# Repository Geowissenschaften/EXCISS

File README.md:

# EXCISS
Experimental Chondrule Formation at the International Space Station 

Documentation is still beeing updated.

The circuit design files are online, the mechanical design files will be next.

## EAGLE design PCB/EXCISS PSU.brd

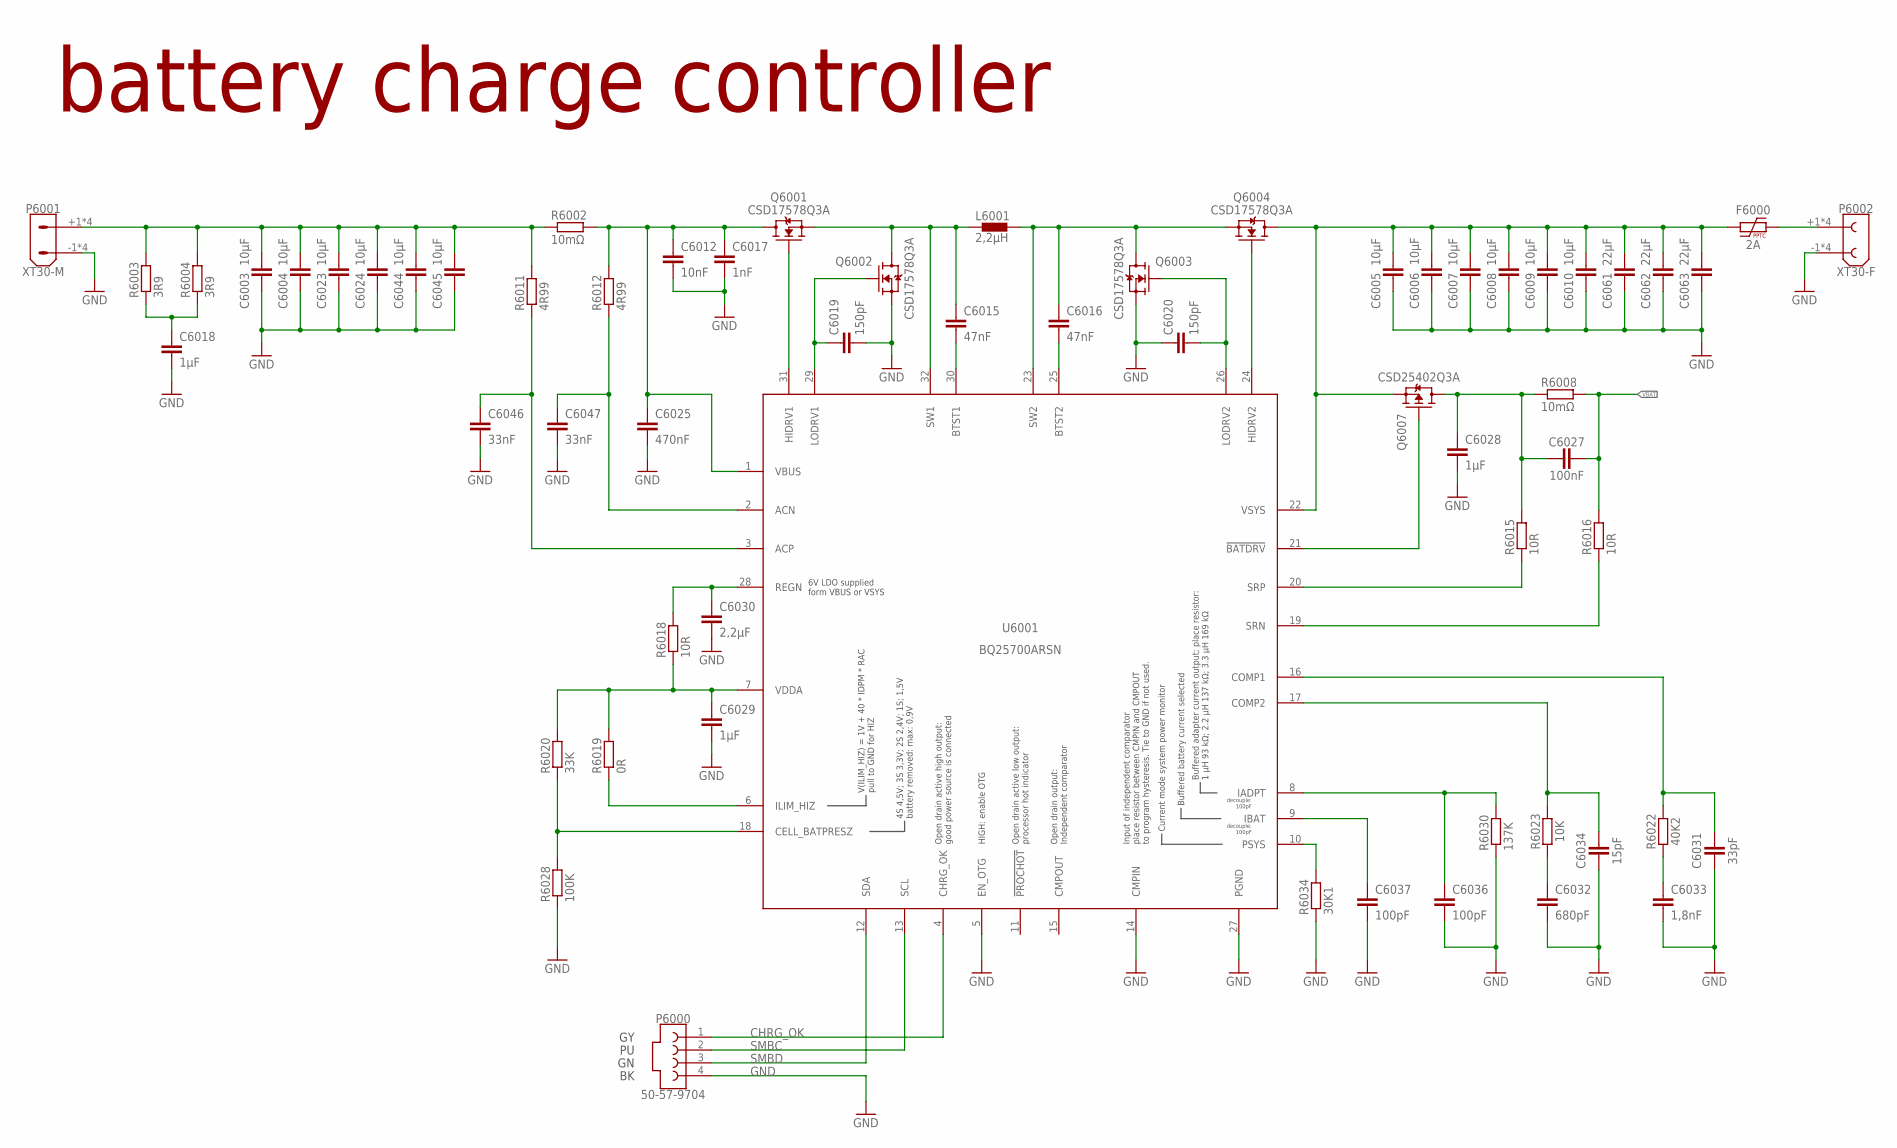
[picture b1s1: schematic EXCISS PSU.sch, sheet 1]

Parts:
C6003, C6004, C6005, C6006, C6007, C6008, C6009, C6010, C6023, C6024, C6044, C6045: 10µF; C0805
C6012: 10nF; C0603
C6015, C6016: 47nF; C0603
C6017: 1nF; C0603
C6018, C6028, C6029: 1µF; C0603
C6019, C6020: 150pF; C0603
C6025: 470nF; C0805
C6027: 100nF; C0603
C6030: 2,2µF; C0603
C6031: 33pF; C0603
C6032: 680pF; C0603
C6033: 1,8nF; C0603
C6034: 15pF; C0603
C6036, C6037: 100pF; C0603
C6046, C6047: 33nF; C0603
C6061, C6062, C6063: 22µF; C1210
F6000: 2A; PTC_1812
L6001: 2,2µH; 8030
P6000: 50-57-9704; RENAME-SIGNAL
P6001: XT30-M; RENAME_XT-CONNECTOR
P6002: XT30-F; RENAME_XT-CONNECTOR
Q6001, Q6002, Q6003, Q6004: CSD17578Q3A; Q3A
Q6007: CSD25402Q3A; Q3A
R6002, R6008: 10mΩ; R1206
R6003, R6004: 3R9; R1206
R6011, R6012: 4R99; R0603
R6015, R6016, R6018: 10R; R0603
R6019: 0R; R0603
R6020: 33K; R0603
R6022: 40K2; R0603
R6023: 10K; R0603
R6028: 100K; R0603
R6030: 137K; R0603
R6034: 30K1; R0603
U6001: BQ25700ARSN; RSN(S-PWQFN-N32)

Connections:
CHRG_OK: P6000.1, U6001.4 (CHRG_OK)
GND: C6003.2, C6004.2, C6005.2, C6006.2, C6007.2, C6008.2, C6009.2, C6010.2, C6012.2, C6017.2, C6018.2, C6019.2, C6020.1, C6023.2, C6024.2, C6025.2, C6028.2, C6029.2, C6030.2, C6031.2, C6032.2, C6033.2, C6034.2, C6036.2, C6037.2, C6044.2, C6045.2, C6046.2, C6047.2, C6061.2, C6062.2, C6063.2, P6000.4, P6001.-1 (-), P6001.-2 (-), P6001.-3 (-), P6001.-4 (-), P6002.-1 (-), P6002.-2 (-), P6002.-3 (-), P6002.-4 (-), Q6002.1 (S), Q6002.2 (S), Q6002.3 (S), Q6003.1 (S), Q6003.2 (S), Q6003.3 (S), R6028.1, R6030.1, R6034.1, U6001.5 (EN_OTG), U6001.14 (CMPIN), U6001.27 (PGND), U6001.TP0 (GND), U6001.TP1 (GND), U6001.TP2 (GND), U6001.TP3 (GND), U6001.TP4 (GND), U6001.TP5 (GND), U6001.TP6 (GND), U6001.TP7 (GND), U6001.TP8 (GND), U6001.TP9 (GND); also elsewhere on the board
ISS_VBUS: C6003.1, C6004.1, C6023.1, C6024.1, C6044.1, C6045.1, P6001.+1 (+), P6001.+2 (+), P6001.+3 (+), P6001.+4 (+), R6002.1, R6003.2, R6004.2, R6011.2; also elsewhere on the board
unnamed: C6018.1, R6003.1, R6004.1
unnamed: Q6007.4 (G), U6001.21 (!BATDRV)
unnamed: C6032.1, R6023.1
unnamed: R6015.1, U6001.20 (SRP)
unnamed: C6027.1, C6028.1, Q6007.1 (D), Q6007.2 (D), Q6007.3 (D), R6008.1, R6015.2
unnamed: R6016.1, U6001.19 (SRN)
unnamed: Q6001.4 (G), U6001.31 (HIDRV1)
unnamed: C6019.1, Q6002.4 (G), U6001.29 (LODRV1)
unnamed: C6015.2, U6001.30 (BTST1)
unnamed: C6016.1, L6001.P$2 (2), Q6003.TP0 (D), Q6003.TP1 (D), Q6003.TP2 (D), Q6003.TP3 (D), Q6003.TP4 (D), Q6003.TP5 (D), Q6003.TP6 (D), Q6003.TP7 (D), Q6004.1 (S), Q6004.2 (S), Q6004.3 (S), U6001.23 (SW2)
unnamed: C6034.1, R6023.2, U6001.17 (COMP2)
unnamed: C6036.1, R6030.2, U6001.8 (IADPT)
unnamed: R6019.1, U6001.6 (ILIM_HIZ)
unnamed: C6033.1, R6022.1
unnamed: C6020.2, Q6003.4 (G), U6001.26 (LODRV2)
unnamed: Q6004.4 (G), U6001.24 (HIDRV2)
unnamed: C6031.1, R6022.2, U6001.16 (COMP1)
unnamed: C6015.1, L6001.P$1 (1), Q6001.1 (S), Q6001.2 (S), Q6001.3 (S), Q6002.TP0 (D), Q6002.TP1 (D), Q6002.TP2 (D), Q6002.TP3 (D), Q6002.TP4 (D), Q6002.TP5 (D), Q6002.TP6 (D), Q6002.TP7 (D), U6001.32 (SW1)
unnamed: R6034.2, U6001.10 (PSYS)
unnamed: C6037.1, U6001.9 (IBAT)
unnamed: C6046.1, R6011.1, U6001.3 (ACP)
unnamed: C6047.1, R6012.1, U6001.2 (ACN)
unnamed: C6016.2, U6001.25 (BTST2)
unnamed: C6012.1, C6017.1, C6025.1, Q6001.TP0 (D), Q6001.TP1 (D), Q6001.TP2 (D), Q6001.TP3 (D), Q6001.TP4 (D), Q6001.TP5 (D), Q6001.TP6 (D), Q6001.TP7 (D), R6002.2, R6012.2, U6001.1 (VBUS)
unnamed: R6020.1, R6028.2, U6001.18 (CELL_BATPRESZ)
REGN: C6030.1, R6018.2, U6001.28 (REGN)
SMBC: P6000.2, U6001.13 (SCL); also elsewhere on the board
SMBD: P6000.3, U6001.12 (SDA); also elsewhere on the board
VBAT: C6027.2, R6008.2, R6016.2; also elsewhere on the board
VDDA: C6029.1, R6018.1, R6019.2, R6020.2, U6001.7 (VDDA)
VSYS_UPS: F6000.P$3 (2), P6002.+1 (+), P6002.+2 (+), P6002.+3 (+), P6002.+4 (+); also elsewhere on the board
VSYS_UPS_PREFUSE: C6005.1, C6006.1, C6007.1, C6008.1, C6009.1, C6010.1, C6061.1, C6062.1, C6063.1, F6000.P$2 (1), Q6004.TP0 (D), Q6004.TP1 (D), Q6004.TP2 (D), Q6004.TP3 (D), Q6004.TP4 (D), Q6004.TP5 (D), Q6004.TP6 (D), Q6004.TP7 (D), Q6007.TP0 (S), Q6007.TP1 (S), Q6007.TP2 (S), Q6007.TP3 (S), Q6007.TP4 (S), Q6007.TP5 (S), Q6007.TP6 (S), Q6007.TP7 (S), U6001.22 (VSYS)

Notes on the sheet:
battery charge controller

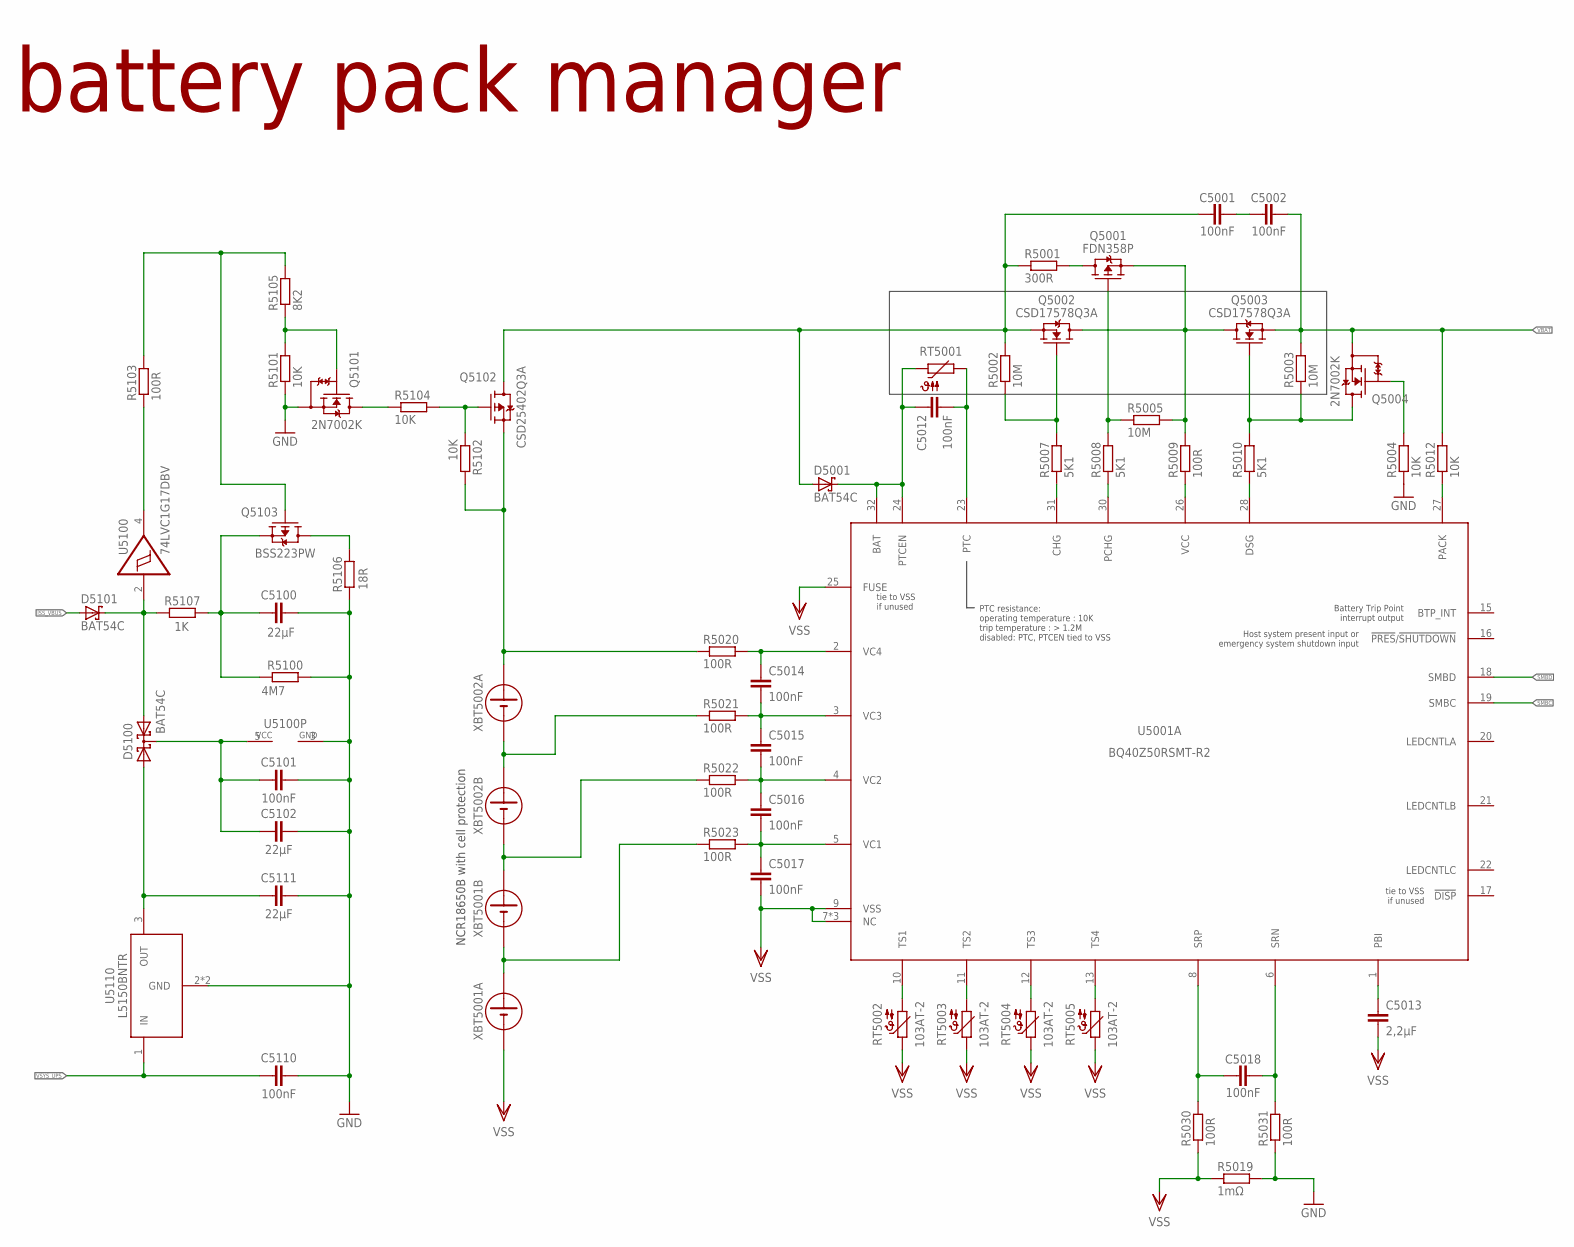
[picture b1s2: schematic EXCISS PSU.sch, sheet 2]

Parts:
C5001, C5002, C5012, C5014, C5015, C5016, C5017, C5018, C5101, C5110: 100nF; C0603
C5013: 2,2µF; C0805
C5100, C5102, C5111: 22µF; C0805
D5001, D5100, D5101: BAT54C; SOT23
Q5001: FDN358P; SOT23-3
Q5002, Q5003: CSD17578Q3A; Q3A
Q5004, Q5101: 2N7002K; SOT23-3
Q5102: CSD25402Q3A; Q3A
Q5103: BSS223PW; DCK(R-PDSO-G3)
R5001: 300R; R2512
R5002, R5003, R5005: 10M; R0603
R5004, R5012, R5101, R5102, R5104: 10K; R0603
R5007, R5008, R5010: 5K1; R0603
R5009, R5020, R5021, R5022, R5023, R5030, R5031, R5103: 100R; R0603
R5019: 1mΩ; R1206
R5100: 4M7; R0805
R5105: 8K2; R0603
R5106: 18R; R0805
R5107: 1K; R0603
RT5001: PRF15BB103RB6RC; 0402
RT5002, RT5003, RT5004, RT5005: 103AT-2; AT-2
U5001: BQ40Z50RSMT-R2; RSM(S-PVQFN-N32)
U5100: 74LVC1G17DBV; SOT23-5
U5110: L5150BNTR; SOT223
XBT5001, XBT5002: KEYSTONE_1049_LONG

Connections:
1P: R5023.1, XBT5001.1+ (+), XBT5001.2- (-)
2P: R5022.1, XBT5001.2+ (+), XBT5002.2- (-)
3P: R5021.1, XBT5002.1- (-), XBT5002.2+ (+)
4P: Q5102.TP0 (S), Q5102.TP1 (S), Q5102.TP2 (S), Q5102.TP3 (S), Q5102.TP4 (S), Q5102.TP5 (S), Q5102.TP6 (S), Q5102.TP7 (S), R5020.1, R5102.2, XBT5002.1+ (+)
4P_SWITCHED: C5001.1, D5001.1 (A), Q5002.1 (S), Q5002.2 (S), Q5002.3 (S), Q5102.1 (D), Q5102.2 (D), Q5102.3 (D), R5001.1, R5002.2
GND: C5100.2, C5101.2, C5102.2, C5110.2, C5111.2, Q5101.2 (S), R5004.1, R5019.2, R5031.1, R5100.1, R5101.1, R5106.2, U5100.3 (GND), U5110.2 (GND), U5110.4 (GND); also elsewhere on the board
ISS_VBUS: D5101.1 (A); also elsewhere on the board
unnamed: Q5102.4 (G), R5102.1, R5104.2
unnamed: R5103.1, U5100.4 (O)
unnamed: Q5101.1 (G), R5101.2, R5105.1
unnamed: Q5101.3 (D), R5104.1
unnamed: C5100.1, Q5103.2 (S), R5100.2, R5107.1
unnamed: R5010.1, U5001.28 (DSG)
unnamed: C5001.2, C5002.1
unnamed: Q5001.2 (S), Q5002.TP0 (D), Q5002.TP1 (D), Q5002.TP2 (D), Q5002.TP3 (D), Q5002.TP4 (D), Q5002.TP5 (D), Q5002.TP6 (D), Q5002.TP7 (D), Q5003.TP0 (D), Q5003.TP1 (D), Q5003.TP2 (D), Q5003.TP3 (D), Q5003.TP4 (D), Q5003.TP5 (D), Q5003.TP6 (D), Q5003.TP7 (D), R5005.2, R5009.2
unnamed: Q5103.3 (D), R5106.1
unnamed: Q5002.4 (G), R5002.1, R5007.2
unnamed: R5007.1, U5001.31 (CHG)
unnamed: Q5001.3 (D), R5001.2
unnamed: Q5001.1 (G), R5005.1, R5008.2
unnamed: R5009.1, U5001.26 (VCC)
unnamed: C5101.1, C5102.1, D5100.3 (CC), U5100.5 (VCC)
unnamed: Q5003.4 (G), Q5004.3 (D), R5003.1, R5010.2
unnamed: R5008.1, U5001.30 (PCHG)
unnamed: Q5004.1 (G), R5004.2
unnamed: R5012.1, U5001.27 (PACK)
unnamed: C5014.1, R5020.2, U5001.2 (VC4)
unnamed: C5014.2, C5015.1, R5021.2, U5001.3 (VC3)
unnamed: C5015.2, C5016.1, R5022.2, U5001.4 (VC2)
unnamed: C5016.2, C5017.1, R5023.2, U5001.5 (VC1)
unnamed: C5013.1, U5001.1 (PBI)
unnamed: C5012.1, D5001.3 (C), RT5001.1, U5001.24 (PTCEN), U5001.32 (BAT)
unnamed: C5012.2, RT5001.2, U5001.23 (PTC)
unnamed: C5018.2, R5031.2, U5001.6 (SRN)
unnamed: C5018.1, R5030.2, U5001.8 (SRP)
unnamed: RT5002.P$2 (2), U5001.10 (TS1)
unnamed: RT5003.P$2 (2), U5001.11 (TS2)
unnamed: RT5004.P$2 (2), U5001.12 (TS3)
unnamed: RT5005.P$2 (2), U5001.13 (TS4)
unnamed: Q5103.1 (G), R5103.2, R5105.2
unnamed: D5100.1 (A1), D5101.3 (C), R5107.2, U5100.2 (I)
OUT: C5111.1, D5100.2 (A2), U5110.3 (OUT)
SMBC: U5001.19 (SMBC); also elsewhere on the board
SMBD: U5001.18 (SMBD); also elsewhere on the board
VBAT: C5002.2, Q5003.1 (S), Q5003.2 (S), Q5003.3 (S), Q5004.2 (S), R5003.2, R5012.2; also elsewhere on the board
VSS: C5013.2, C5017.2, R5019.1, R5030.1, RT5002.P$1 (1), RT5003.P$1 (1), RT5004.P$1 (1), RT5005.P$1 (1), U5001.7 (NC), U5001.9 (VSS), U5001.14 (NC), U5001.25 (FUSE), U5001.29 (NC), U5001.TP0 (VSS), U5001.TP1 (VSS), XBT5001.1- (-)
VSYS_UPS: C5110.1, U5110.1 (IN); also elsewhere on the board

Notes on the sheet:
battery pack manager
NCR18650B with cell protection

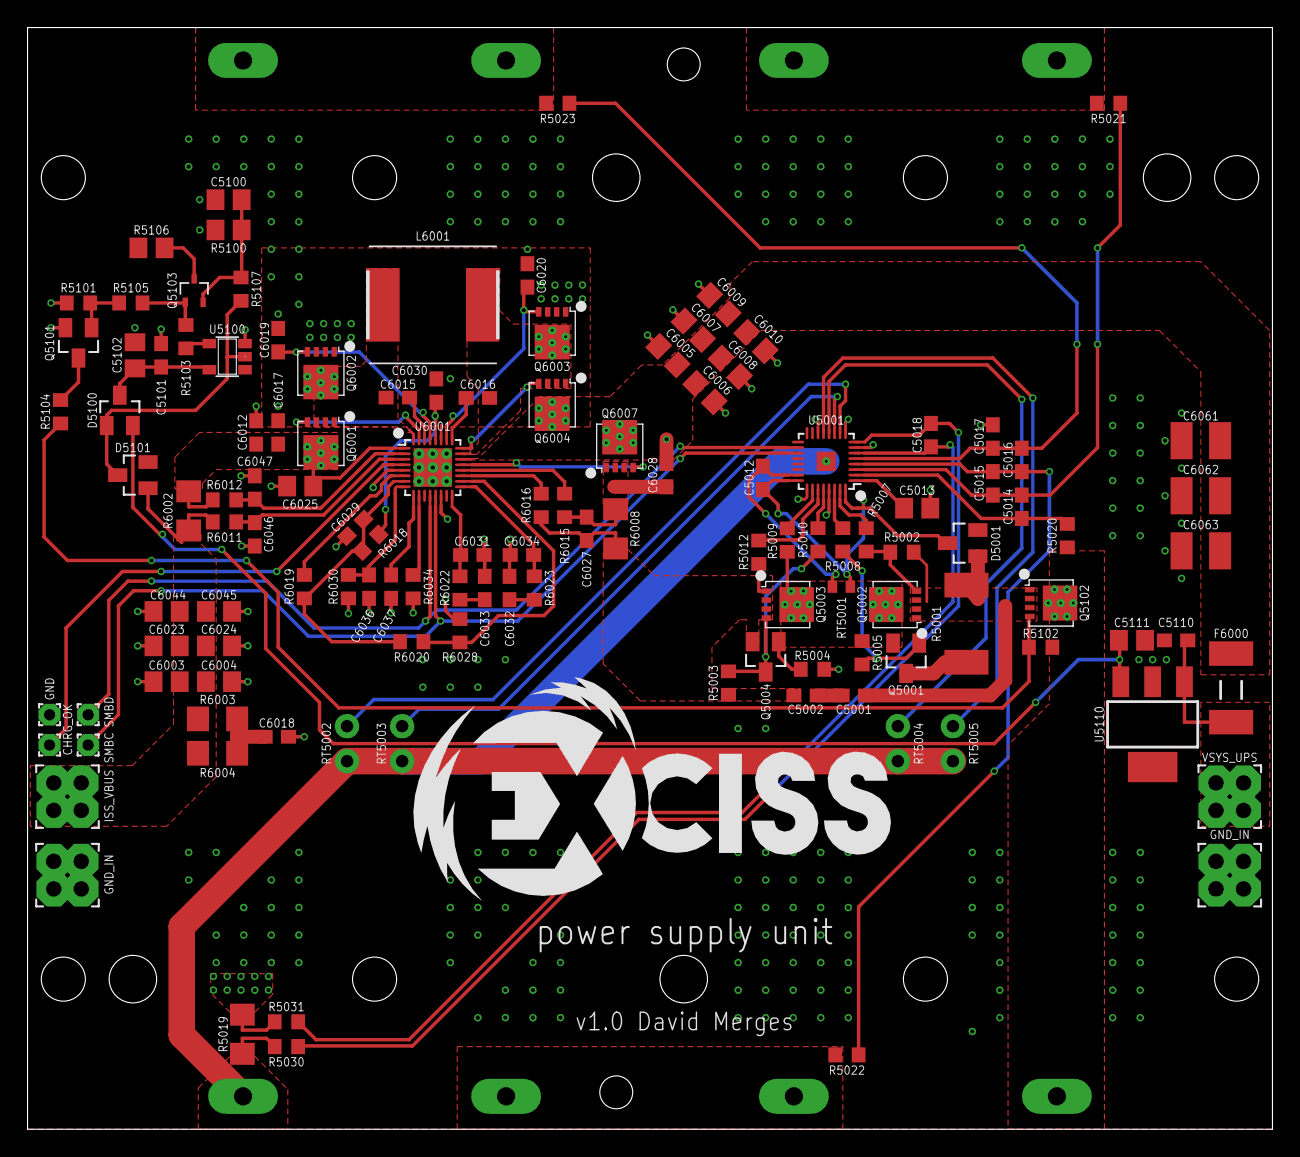
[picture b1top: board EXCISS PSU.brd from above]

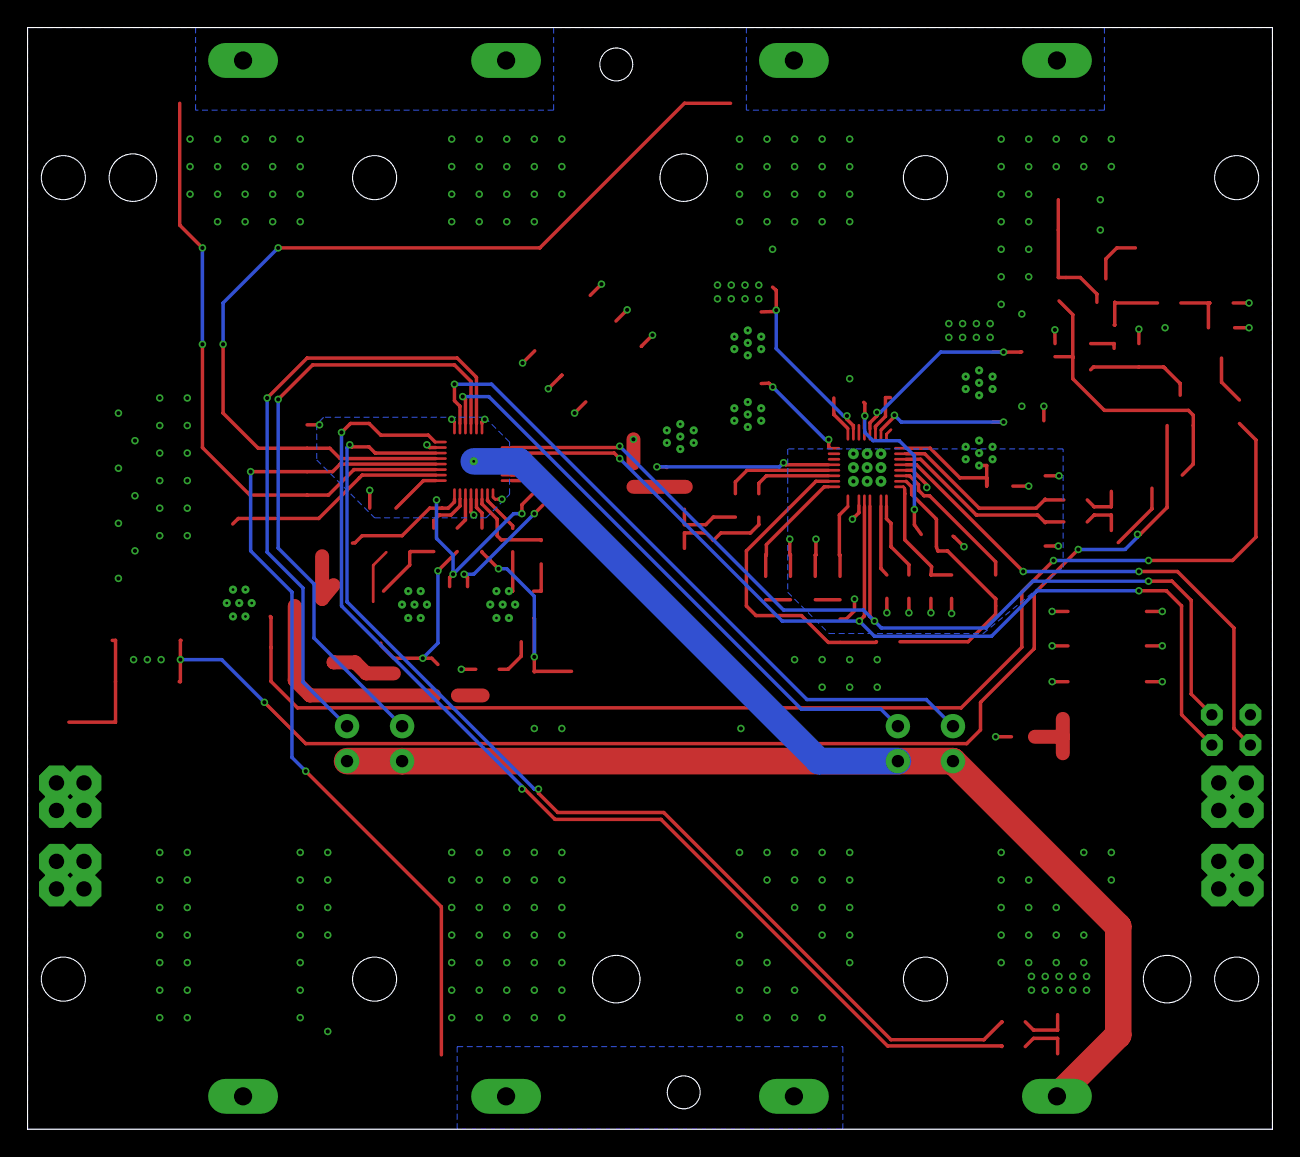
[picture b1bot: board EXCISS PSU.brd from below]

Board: 2 copper layers, 90.4 x 80.0 mm, 126 parts (2 on the bottom side), 76 nets.

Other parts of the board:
U$1, U$2, U$3, U$4: DRILL_M3_SPACER
U$5: LOGO_EXCISS

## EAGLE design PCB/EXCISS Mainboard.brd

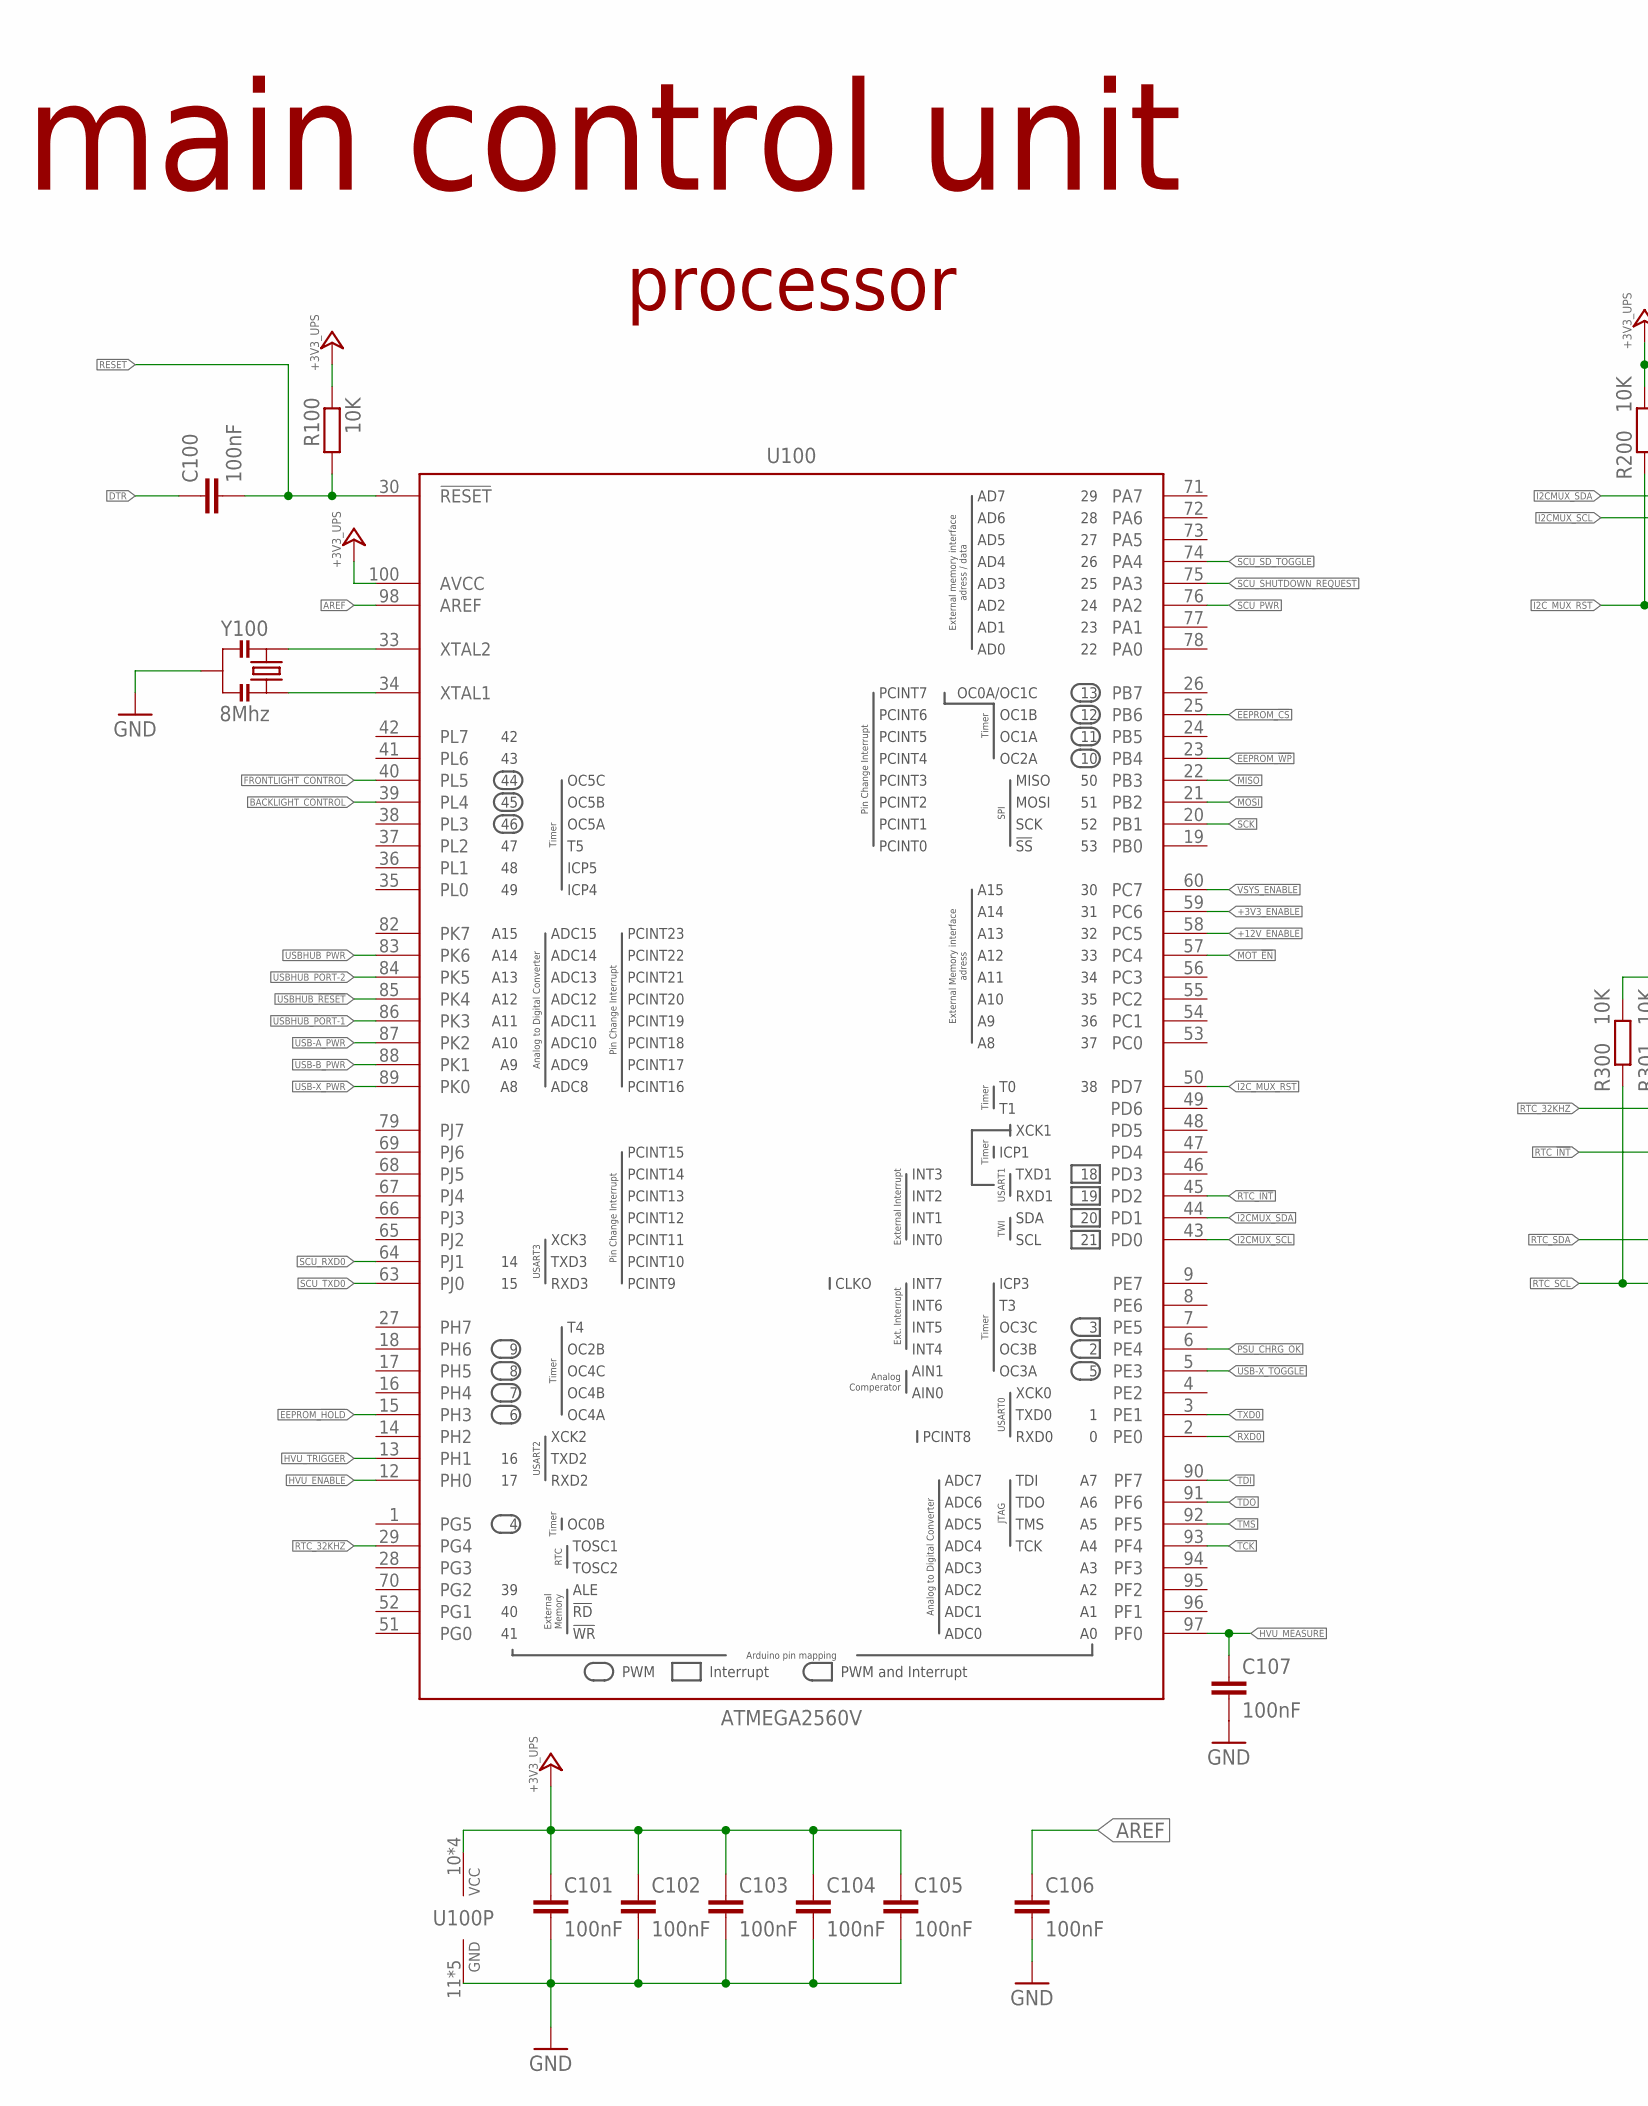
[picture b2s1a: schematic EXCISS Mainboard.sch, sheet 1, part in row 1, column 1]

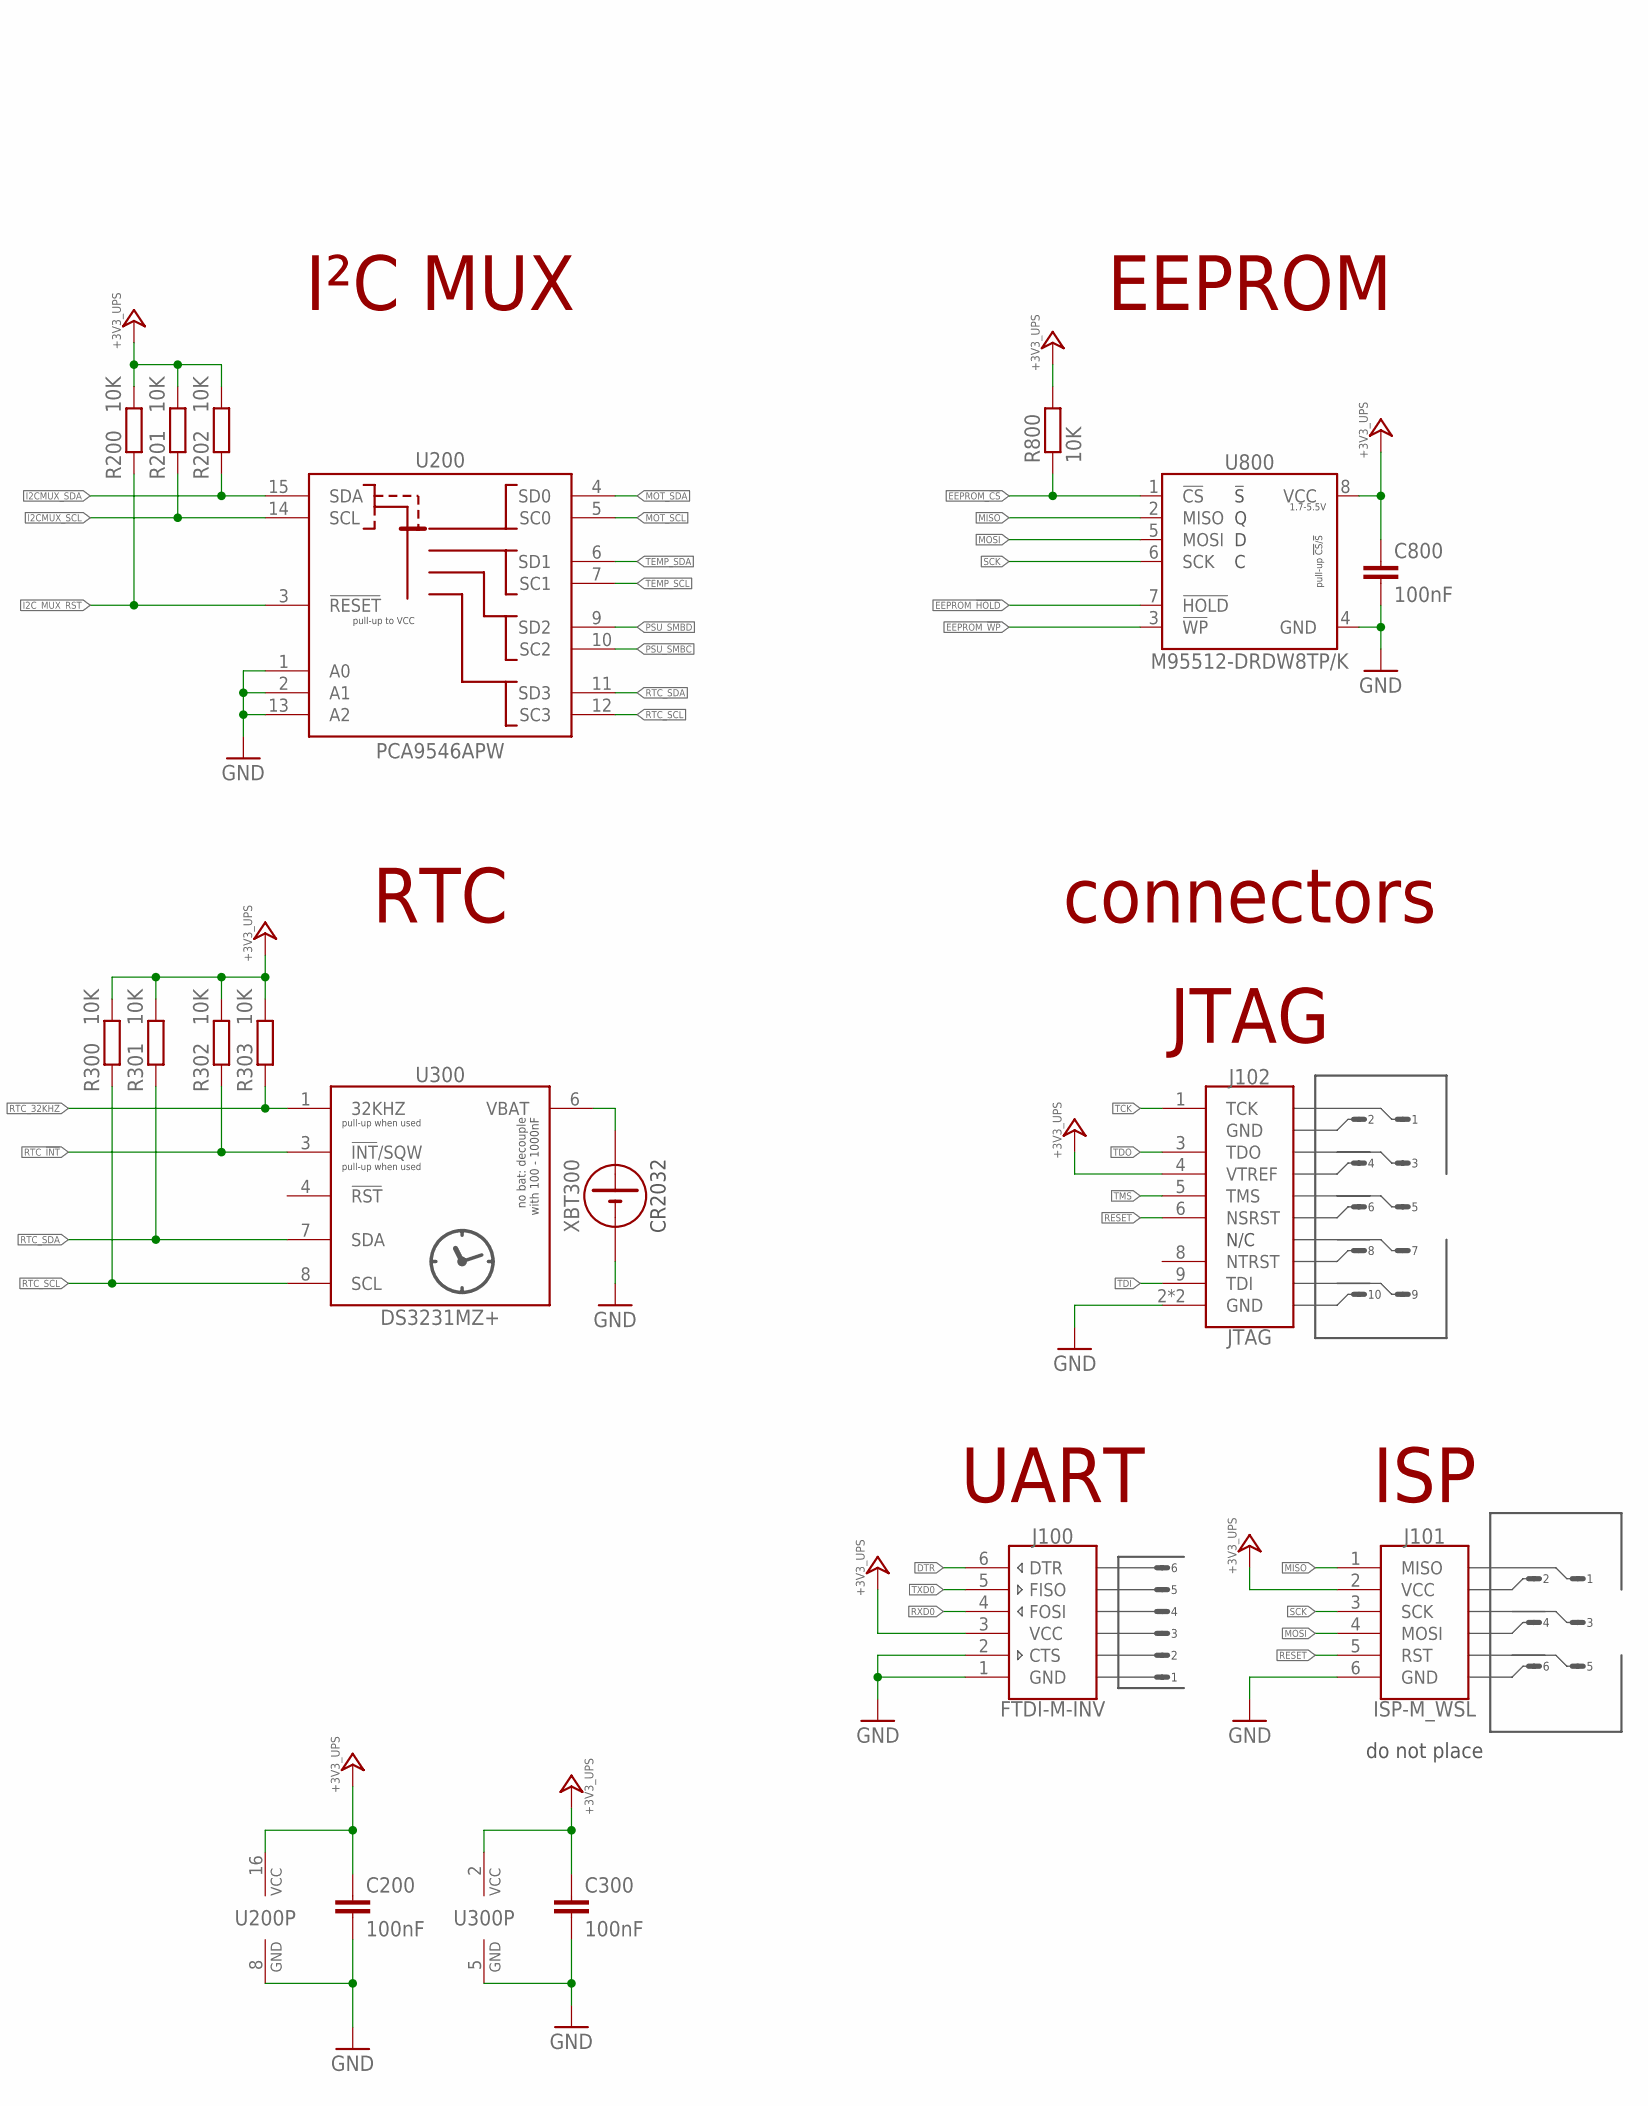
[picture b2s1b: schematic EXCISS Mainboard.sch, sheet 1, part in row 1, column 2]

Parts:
C100, C101, C102, C103, C104, C105, C106, C107, C200, C300, C800: 100nF; C0603
J100: FTDI-M-INV; MPE_094-1-006
J101: ISP-M_WSL; ISP-M-THT
J102: JTAG; 20021521-00010T1LF
R100, R200, R201, R202, R300, R301, R302, R303, R800: 10K; R0603
U100: ATMEGA2560V; TQFP100
U200: PCA9546APW; R-PDSO-G16
U300: DS3231MZ+; SOIC8
U800: M95512-DRDW8TP/K; TSSOP8
XBT300: KEYSTONE_1070
Y100: 8Mhz; CSTNE

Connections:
+3V3_ENABLE: U100.59 (PC6); also elsewhere on the board
+3V3_UPS: C101.1, C102.1, C103.1, C104.1, C105.1, C200.1, C300.1, C800.1, J100.3 (VCC), J101.2 (VCC), J102.4 (VTREF), R100.1, R200.1, R201.1, R202.1, R300.1, R301.1, R302.1, R303.1, R800.2, U100.10 (VCC), U100.31 (VCC), U100.61 (VCC), U100.80 (VCC), U100.100 (AVCC), U200.16 (VCC), U300.2 (VCC), U800.8 (VCC); also elsewhere on the board
+12V_ENABLE: U100.58 (PC5); also elsewhere on the board
AREF: C106.1, U100.98 (AREF)
BACKLIGHT_CONTROL: U100.39 (PL4); also elsewhere on the board
DTR: C100.1, J100.6 (DTR)
EEPROM_!CS: R800.1, U100.25 (PB6), U800.1 (!CS)
EEPROM_!HOLD: U100.15 (PH3), U800.7 (!HOLD)
EEPROM_!WP: U100.23 (PB4), U800.3 (!WP)
FRONTLIGHT_CONTROL: U100.40 (PL5); also elsewhere on the board
GND: C101.2, C102.2, C103.2, C104.2, C105.2, C106.2, C107.2, C200.2, C300.2, C800.2, J100.1 (GND), J100.2 (CTS), J101.6 (GND), J102.2 (GND), J102.10 (GND), U100.11 (GND), U100.32 (GND), U100.62 (GND), U100.81 (GND), U100.99 (GND), U200.1 (A0), U200.2 (A1), U200.8 (GND), U200.13 (A2), U300.5 (GND), U800.4 (GND), XBT300.-, Y100.2; also elsewhere on the board
HVU_ENABLE: U100.12 (PH0); also elsewhere on the board
HVU_MEASURE: C107.1, U100.97 (PF0); also elsewhere on the board
HVU_TRIGGER: U100.13 (PH1); also elsewhere on the board
I2CMUX_SCL: R201.2, U100.43 (PD0), U200.14 (SCL)
I2CMUX_SDA: R202.2, U100.44 (PD1), U200.15 (SDA)
I2C_MUX_RST: R200.2, U100.50 (PD7), U200.3 (!RESET)
MISO: J101.1 (MISO), U100.22 (PB3), U800.2 (MISO)
MOSI: J101.4 (MOSI), U100.21 (PB2), U800.5 (MOSI)
MOT_!EN: U100.57 (PC4); also elsewhere on the board
MOT_SCL: U200.5 (SC0); also elsewhere on the board
MOT_SDA: U200.4 (SD0); also elsewhere on the board
unnamed: U300.6 (VBAT), XBT300.+
unnamed: U100.33 (XTAL2), Y100.1
unnamed: U100.34 (XTAL1), Y100.3
PSU_CHRG_OK: U100.6 (PE4); also elsewhere on the board
PSU_SMBC: U200.10 (SC2); also elsewhere on the board
PSU_SMBD: U200.9 (SD2); also elsewhere on the board
RESET: C100.2, J101.5 (RST), J102.6 (NSRST), R100.2, U100.30 (!RESET!)
RTC_32KHZ: R303.2, U100.29 (PG4), U300.1 (32KHZ)
RTC_!INT: R302.2, U100.45 (PD2), U300.3 (!INT!/SQW)
RTC_SCL: R300.2, U200.12 (SC3), U300.8 (SCL)
RTC_SDA: R301.2, U200.11 (SD3), U300.7 (SDA)
RXD0: J100.4 (FOSI), U100.2 (PE0)
SCK: J101.3 (SCK), U100.20 (PB1), U800.6 (SCK)
SCU_PWR: U100.76 (PA2); also elsewhere on the board
SCU_RXD0: U100.64 (PJ1); also elsewhere on the board
SCU_SD_TOGGLE: U100.74 (PA4); also elsewhere on the board
SCU_SHUTDOWN_REQUEST: U100.75 (PA3); also elsewhere on the board
SCU_TXD0: U100.63 (PJ0); also elsewhere on the board
TCK: J102.1 (TCK), U100.93 (PF4)
TDI: J102.9 (TDI), U100.90 (PF7)
TDO: J102.3 (TDO), U100.91 (PF6)
TEMP_SCL: U200.7 (SC1); also elsewhere on the board
TEMP_SDA: U200.6 (SD1); also elsewhere on the board
TMS: J102.5 (TMS), U100.92 (PF5)
TXD0: J100.5 (FISO), U100.3 (PE1)
USB-A_PWR: U100.87 (PK2); also elsewhere on the board
USB-B_PWR: U100.88 (PK1); also elsewhere on the board
USB-X_PWR: U100.89 (PK0); also elsewhere on the board
USB-X_TOGGLE: U100.5 (PE3); also elsewhere on the board
USBHUB_!RESET: U100.85 (PK4); also elsewhere on the board
USBHUB_PORT-1: U100.86 (PK3); also elsewhere on the board
USBHUB_PORT-2: U100.84 (PK5); also elsewhere on the board
USBHUB_PWR: U100.83 (PK6); also elsewhere on the board
VSYS_ENABLE: U100.60 (PC7); also elsewhere on the board

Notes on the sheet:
main control unit
connectors
I²C MUX
processor
JTAG
UART
ISP
RTC
CR2032
EEPROM
do not place

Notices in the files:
parts and their libraries:
microbuilder: This work is placed in the public domain, and may be freely used for commercial and non-commercial work with the following conditions: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
